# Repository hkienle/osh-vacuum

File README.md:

# Open Source Vacuum Cleaner

> **📝 Note:** This repository is currently being populated with information. Content and documentation are being added progressively.

---

## About

This repository contains the Open Source Vacuum Cleaner project, an open-source hardware and software solution for building custom vacuum cleaners. The project includes complete PCB designs, ESP32-S3 based firmware, and a web-based control interface.

The system is designed to control high RPM impellers for vacuum machines, featuring motor control, real-time monitoring (RPM, temperature, battery voltage), WiFi connectivity, and a modern web interface.

## Project Structure

```
osh-vacuum/
├── Hardware/                  # PCB designs and hardware documentation
│   ├── v1/                    # Benchtop prototype board (V1)
│   │   ├── README.md          # Hardware documentation and BOM
│   │   └── Production/        # Manufacturing files
│   └── v2/                    # V2 electronics (KiCad 10)
│       ├── README.md          # Overview, cabling, commit marking
│       ├── Main PCB/          # Control board, JLCPCB data in Production/
│       └── HMI PCB/           # Breakaway LED strips and buttons, JLCPCB data in Production/
├── Firmware/                  # ESP32-S3 firmware
│   ├── v1/                    # Firmware for hardware V1 (with React web interface in ui/)
│   └── v2/                    # Firmware for hardware V2 (not started yet)
└── README.md                  # This file
```

### Hardware

**V1 – benchtop prototype**
- ESP32-S3 microcontroller with WiFi and BLE
- Motor control with Infineon ProFet for high-side switching
- 5 RGB LEDs (WS2812B) and 3 customizable buttons
- Battery voltage monitoring (15-32V input)
- Temperature monitoring via thermistor
- Tachometer input for RPM measurement
- Break-off sections for flexible form factors

📖 **[Hardware V1 Documentation →](Hardware/v1/README.md)**

**V2 – main board and HMI boards** (first batch ordered November 2026, untested)
- Main PCB: XT60 battery input with fuse, TVS and current measurement (INA237), ESP32-S3 with USB-C, switched motor output (XT60) for an ESC, brush output, motor signal connector with selectable 3.3 V / 5 V level, 4 × Qwiic, NTC, expansion header
- HMI PCB: breakaway panel with two WS2812B LED strips and button boards, connected to the main board with JST PH cables

📖 **[Hardware V2 Documentation →](Hardware/v2/README.md)**

### Firmware

The firmware provides:
- Motor speed control (0-100% PWM)
- Real-time monitoring (RPM, temperature, battery voltage)
- WiFi access point with web server
- WebSocket communication for live updates
- React-based web interface

The firmware in [Firmware/v1](Firmware/v1/README.md) is written for hardware V1. Firmware for V2 will go into `Firmware/v2`.

📖 **[Firmware Documentation →](Firmware/v1/README.md)**

## Quick Start

1. **Hardware**: Review the PCB documentation for [V1](Hardware/v1/README.md) or [V2](Hardware/v2/README.md)
2. **Firmware**: Follow the [firmware build and upload instructions](Firmware/v1/Setup.md)
3. **Frontend**: Build and upload the web interface as described in the firmware README

## Status

**Current Phase**: Benchtop Prototype (V1), V2 boards ordered

The V2 boards (main board and HMI boards) are ordered but untested; firmware for V2 has not been started yet. All designs and firmware are provided as-is for development and testing purposes.

---

*More information at [HackMD - Team Intuity](https://hackmd.io/@team-intuity) and [HackMD - hkienle](https://hackmd.io/@hkienle)*

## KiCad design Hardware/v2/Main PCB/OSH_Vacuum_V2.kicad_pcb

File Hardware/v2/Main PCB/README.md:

# Main PCB (Hardware V2)

Control board of the vacuum cleaner: battery input, motor and brush switching, ESP32-S3, sensors and all connectors.
KiCad 10 project `OSH_Vacuum_V2.kicad_pro`, schematic as PDF in [OSH_Vacuum_V2.pdf](OSH_Vacuum_V2.pdf).

**Status:** first batch ordered at JLCPCB in November 2026, not yet tested.

## Board

- 68 × 90 mm, 4 layers, 1.6 mm, 2 oz outer / 1 oz inner copper
- All parts on the top side, all parts in stock at JLCPCB (LCSC number in every symbol)
- Four M3 mounting holes (plated, connected to GND)

## Blocks

| Schematic sheet | Content |
|---|---|
| `Versorgung.kicad_sch` (power) | XT60 battery input (J10), 25 A fuse, TVS, 1 mΩ shunt with INA237 (current and battery voltage), LMR36520 buck to 5 V, USB/5 V diode OR, LDL1117 3.3 V, AP2553 switched outputs |
| `MCU_USB.kicad_sch` | ESP32-S3-WROOM-1-N16R8, USB-C with ESD protection, reset and boot buttons |
| `Motor_Buerste.kicad_sch` (motor and brush) | High-side motor switch (LM74502 + MOSFET, soft start) to the motor XT60 (J20) for an ESC, brush output with P-MOSFET and freewheel diodes (terminal J22), status LEDs |
| `Motorsignale_I2C_NTC.kicad_sch` | Motor signal connector J61 (JST PH 5-pin): signal level V_MOT 3.3 V by default, 5 V selectable with JP60; level shifters and protected inputs. I2C bus with 4 × Qwiic/STEMMA QT, NTC input |
| `Bedienung_CAN_EXP.kicad_sch` (user interface, expansion) | WS2812B LED output J60, three buttons (on board and via JST PH J50–J52), expansion header 2 × 7 (J40) |

## Connectors to the HMI PCB

JST PH 2.0 mm, pinout 1:1 with the [HMI PCB](../HMI%20PCB/README.md), so use straight cables (pin 1 to pin 1):

| Connector | Pin 1 | Pin 2 | Pin 3 |
|---|---|---|---|
| LED (J60) | GND | Data | 5 V |
| Button (J50–J52) | Switch | GND | – |

A reversed cable swaps 5 V and GND on the LED strips.

## Files

| Path | Content |
|---|---|
| `OSH_Vacuum_V2.kicad_pro`, `*.kicad_sch`, `OSH_Vacuum_V2.kicad_pcb` | KiCad 10 project |
| `OSH_Bedien/Motor/Power.kicad_sym`, `OSH_Vacuum_V2.pretty/` | Project symbols and footprints (linked via `${KIPRJMOD}`) |
| `OSH_Vacuum_V2.3dshapes/` | 3D models that KiCad does not ship (JLCEDA/EasyEDA library or simplified approximations) |
| `Production/` | JLCPCB data: Gerber ZIP (plus unpacked `gerber/`), BOM, CPL |

## Ordering at JLCPCB

Upload `Production/OSH_Vacuum_V2_gerber.zip`, then BOM and CPL for assembly.

- 4 layers, 1.6 mm, 2 oz outer / 1 oz inner, vias plugged, min. via 0.3 / (0.4/0.45) mm
- PCBA top side, parts selected by customer, "Confirm Parts Placement": yes
- In the placement preview, check the orientation of all diodes, ICs and connectors before confirming.

The bottom silkscreen carries `COMMIT xxxxxxx`, see [Hardware V2](../README.md#commit-marking).

## Known issues

- **Boards marked `COMMIT 04D906B`:** on the bottom silkscreen, `+` and `−` are swapped at both XT60 connectors
  (BATTERY IN and MAIN (15A)). The upper pin (square pad) is **GND**, the lower pin is **+**. Only the print is wrong;
  copper and connectors are correct. Fixed in `31ACDF0`.

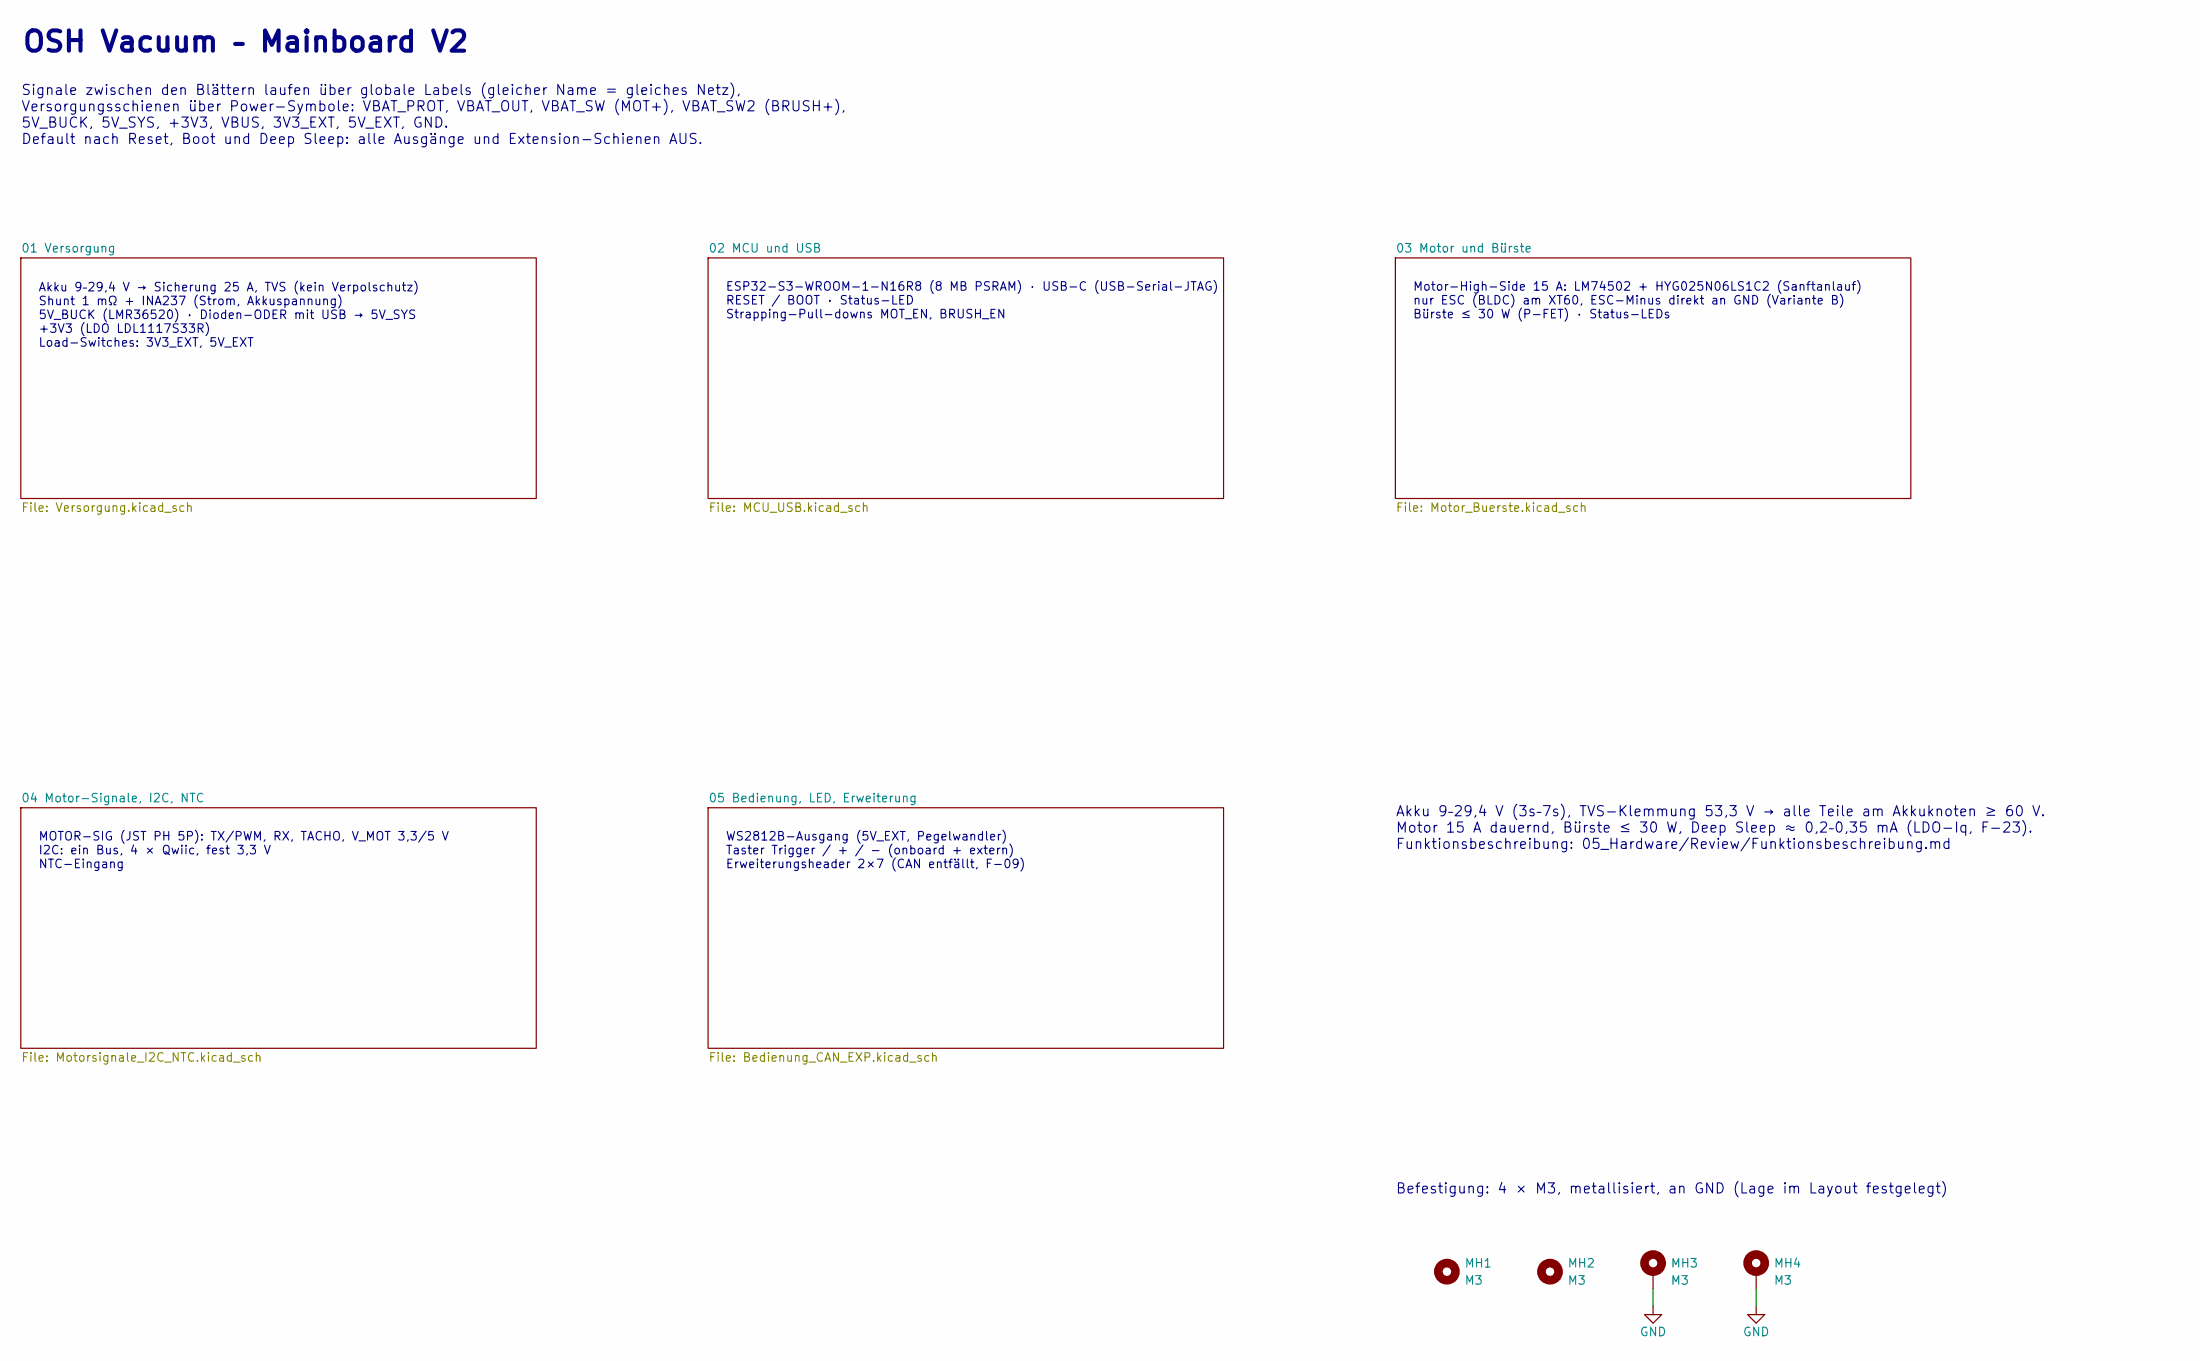
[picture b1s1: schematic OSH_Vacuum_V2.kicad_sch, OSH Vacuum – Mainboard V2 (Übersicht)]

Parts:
MH1, MH2: M3; MountingHole_3.2mm_M3_SilkRing
MH3, MH4: M3; MountingHole_3.2mm_M3_Pad_Via

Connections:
GND: MH3.1, MH4.1; also elsewhere on the board

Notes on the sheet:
ESP32-S3-WROOM-1-N16R8 (8 MB PSRAM) · USB-C (USB-Serial-JTAG) RESET / BOOT · Status-LED Strapping-Pull-downs MOT_EN, BRUSH_EN
OSH Vacuum – Mainboard V2
Motor-High-Side 15 A: LM74502 + HYG025N06LS1C2 (Sanftanlauf) nur ESC (BLDC) am XT60, ESC-Minus direkt an GND (Variante B) Bürste ≤ 30 W (P-FET) · Status-LEDs
Signale zwischen den Blättern laufen über globale Labels (gleicher Name = gleiches Netz), Versorgungsschienen über Power-Symbole: VBAT_PROT, VBAT_OUT, VBAT_SW (MOT+), VBAT_SW2 (BRUSH+), 5V_BUCK, 5V_SYS, +3V3, VBUS, 3V3_EXT, 5V_EXT, GND. Default nach Reset, Boot und Deep Sleep: alle Ausgänge und Ext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
MOTOR-SIG (JST PH 5P): TX/PWM, RX, TACHO, V_MOT 3,3/5 V I2C: ein Bus, 4 × Qwiic, fest 3,3 V NTC-Eingang
Akku 9–29,4 V (3s–7s), TVS-Klemmung 53,3 V → alle Teile am Akkuknoten ≥ 60 V. Motor 15 A dauernd, Bürste ≤ 30 W, Deep Sleep ≈ 0,2–0,35 mA (LDO-Iq, F-23). Funktionsbeschreibung: 05_Hardware/Review/Funktionsbeschreibung.md
WS2812B-Ausgang (5V_EXT, Pegelwandler) Taster Trigger / + / − (onboard + extern) Erweiterungsheader 2×7 (CAN entfällt, F-09)
Befestigung: 4 × M3, metallisiert, an GND (Lage im Layout festgelegt)
Akku 9–29,4 V → Sicherung 25 A, TVS (kein Verpolschutz) Shunt 1 mΩ + INA237 (Strom, Akkuspannung) 5V_BUCK (LMR36520) · Dioden-ODER mit USB → 5V_SYS +3V3 (LDO LDL1117S33R) Load-Switches: 3V3_EXT, 5V_EXT

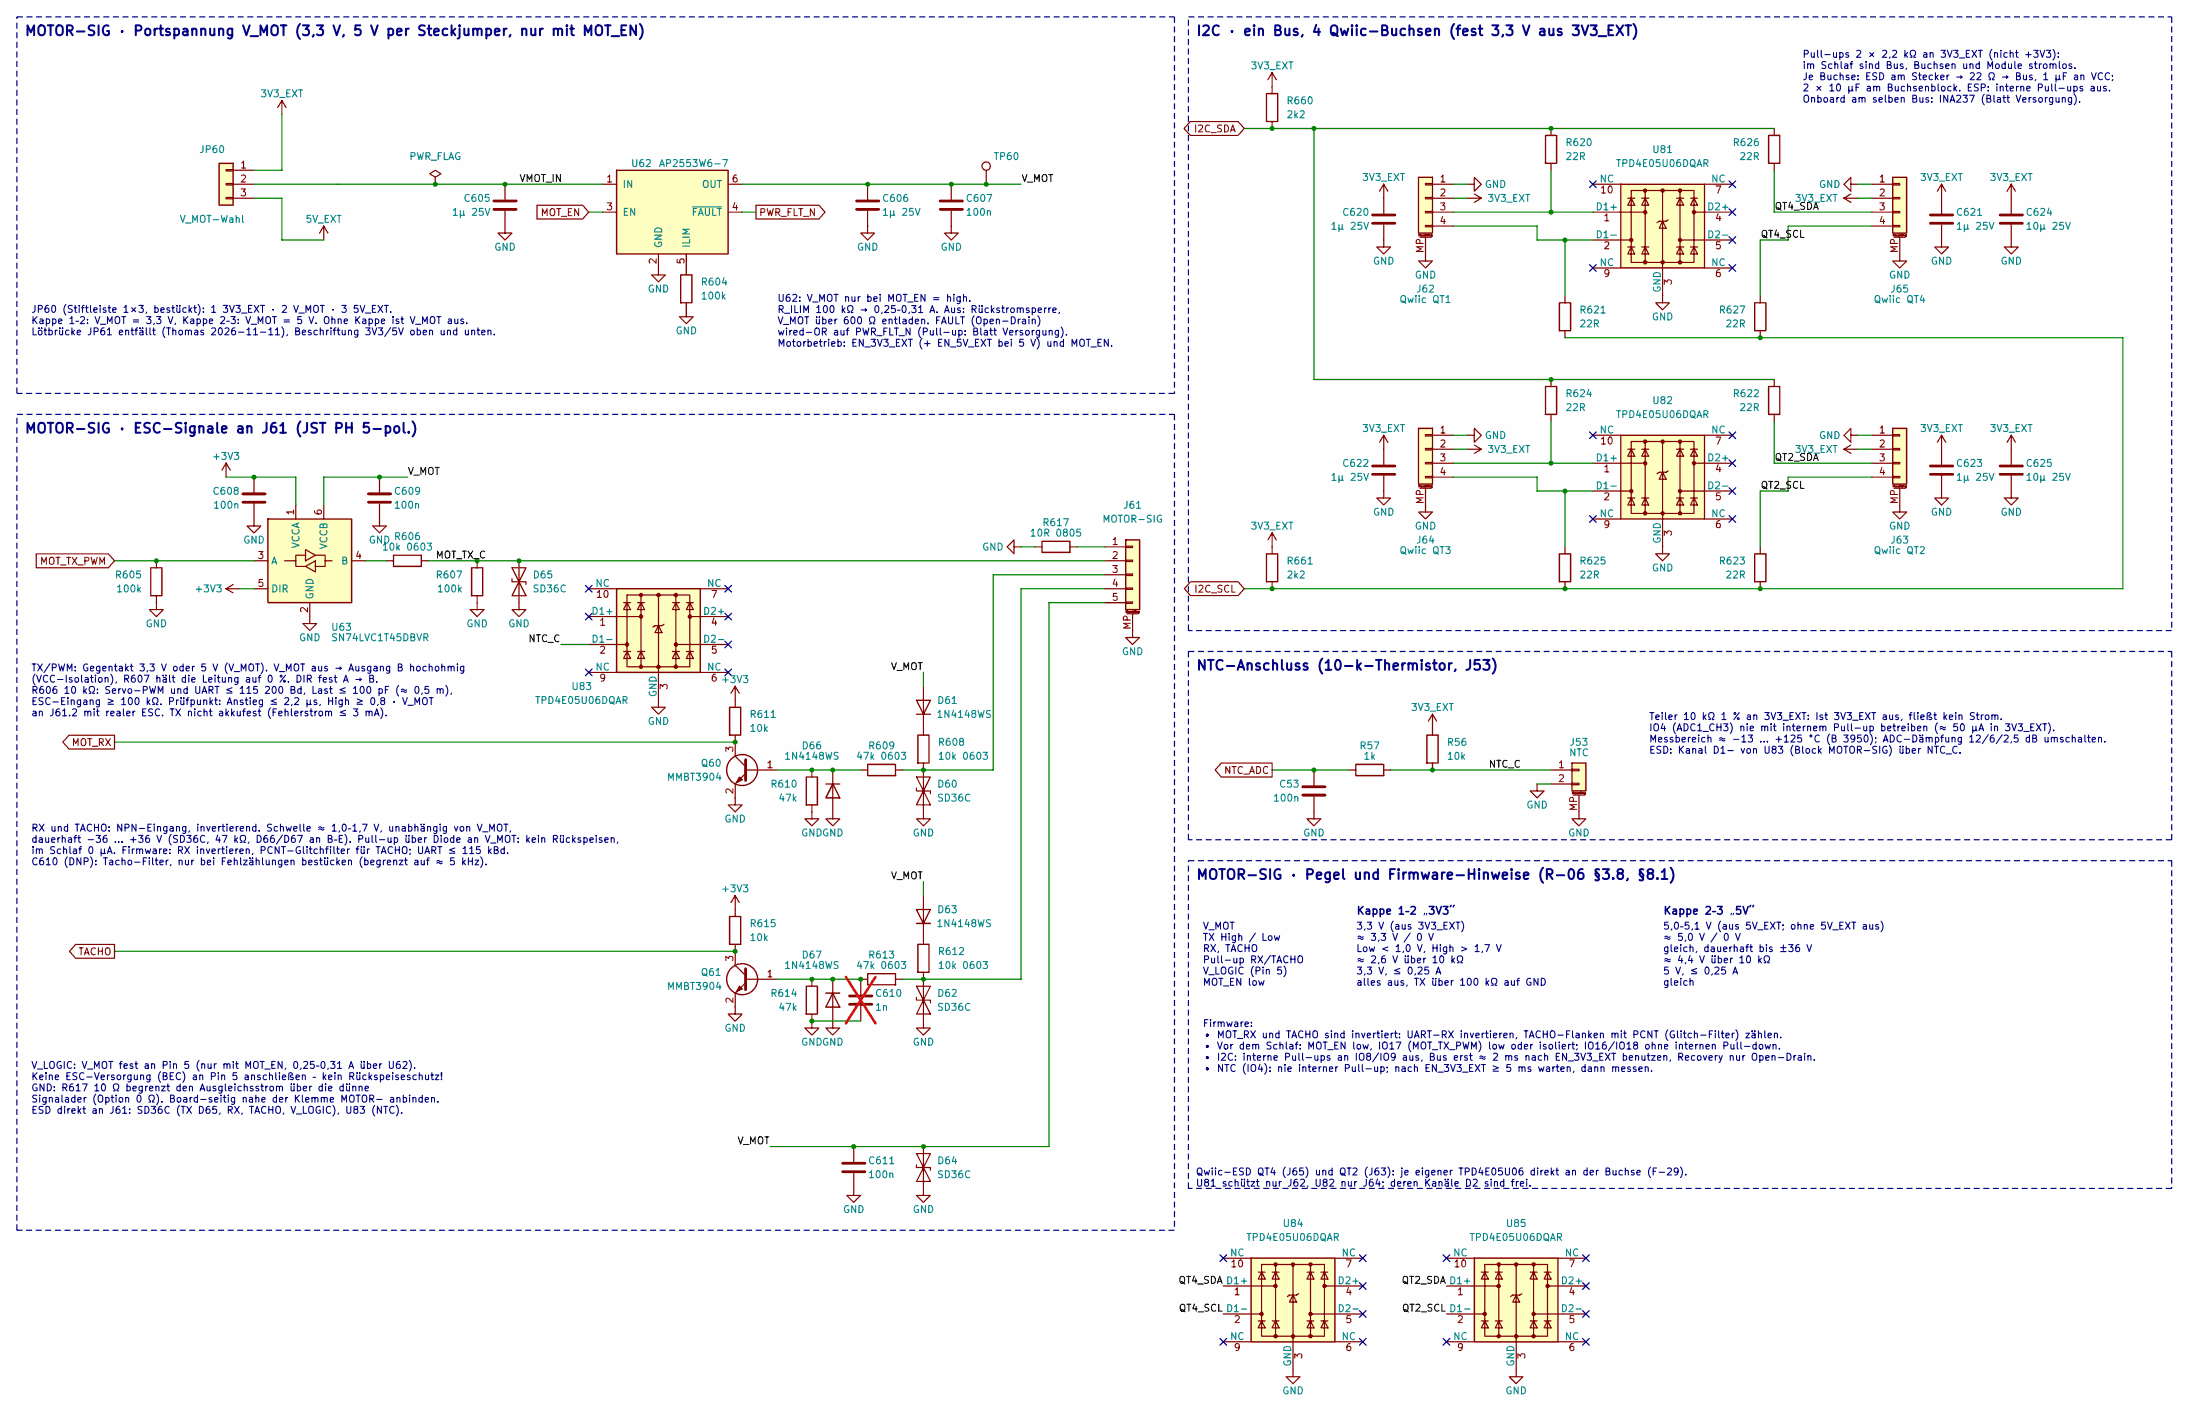
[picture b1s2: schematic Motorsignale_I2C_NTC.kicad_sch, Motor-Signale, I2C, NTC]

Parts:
C53, C607, C608, C609, C611: 100n; C_0402_1005Metric; MPN CL05B104KO5NNNC; LCSC C1525
C605, C606, C620, C621, C622, C623: 1µ 25V; C_0402_1005Metric; MPN CL05A105KA5NQNC; LCSC C52923
C610: 1n; C_0402_1005Metric; MPN 0402B102K500NT; LCSC C1523; not fitted
C624, C625: 10µ 25V; C_0805_2012Metric; MPN CL21A106KAYNNNE; LCSC C15850
D60, D62, D64, D65: SD36C; D_SOD-323; MPN SD36C; LCSC C502537
D61, D63, D66, D67: 1N4148WS; D_SOD-323; MPN 1N4148WS; LCSC C2128
J53: NTC; JST_PH_S2B-PH-SM4-TB_1x02-1MP_P2.00mm_Horizontal; MPN S2B-PH-SM4-TB(LF)(SN); LCSC C295747
J61: MOTOR-SIG; JST_PH_S5B-PH-SM4-TB_1x05-1MP_P2.00mm_Horizontal; MPN S5B-PH-SM4-TB(LF)(SN); LCSC C265104
J62: Qwiic QT1; Megastar_ZX-SH1.0-4PWT_1x04-1MP_P1.00mm_Horizontal; MPN ZX-SH1.0-4PWT; LCSC C7430446
J63: Qwiic QT2; Megastar_ZX-SH1.0-4PWT_1x04-1MP_P1.00mm_Horizontal; MPN ZX-SH1.0-4PWT; LCSC C7430446
J64: Qwiic QT3; Megastar_ZX-SH1.0-4PWT_1x04-1MP_P1.00mm_Horizontal; MPN ZX-SH1.0-4PWT; LCSC C7430446
J65: Qwiic QT4; Megastar_ZX-SH1.0-4PWT_1x04-1MP_P1.00mm_Horizontal; MPN ZX-SH1.0-4PWT; LCSC C7430446
JP60: V_MOT-Wahl; PinHeader_1x03_P2.54mm_Vertical; MPN B-2100S03P-A110; LCSC C124376
Q60, Q61: MMBT3904; SOT-23; MPN MMBT3904 (RANGE:100-300); LCSC C20526
R56, R611, R615: 10k; R_0402_1005Metric; MPN 0402WGF1002TCE; LCSC C25744
R57: 1k; R_0402_1005Metric; MPN 0402WGF1001TCE; LCSC C11702
R604, R605, R607: 100k; R_0402_1005Metric; MPN 0402WGF1003TCE; LCSC C25741
R606, R608, R612: 10k 0603; R_0603_1608Metric; MPN 0603WAF1002T5E; LCSC C25804
R609, R613: 47k 0603; R_0603_1608Metric; MPN 0603WAF4702T5E; LCSC C25819
R610, R614: 47k; R_0402_1005Metric; MPN 0402WGF4702TCE; LCSC C25792
R617: 10R 0805; R_0805_2012Metric; MPN 0805W8F100JT5E; LCSC C17415
R620, R621, R622, R623, R624, R625, R626, R627: 22R; R_0402_1005Metric; MPN 0402WGF220JTCE; LCSC C25092
R660, R661: 2k2; R_0402_1005Metric; MPN 0402WGF2201TCE; LCSC C25879
TP60: V_MOT; Testpad_D1.0mm
U62: AP2553W6-7; SOT-23-6; MPN AP2553W6-7; LCSC C212302
U63: SN74LVC1T45DBVR; SOT-23-6; MPN SN74LVC1T45DBVR; LCSC C7843
U81, U82, U83, U84, U85: TPD4E05U06DQAR; USON-10_2.5x1.0mm_P0.5mm; MPN TPD4E05U06DQAR; LCSC C138714

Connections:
3V3_EXT: C620.1, C621.1, C622.1, C623.1, C624.1, C625.1, J62.2, J63.2, J64.2, J65.2, JP60.1, R56.1, R660.1, R661.1; also elsewhere on the board
5V_EXT: JP60.3; also elsewhere on the board
+3V3: C608.1, R611.1, R615.1, U63.1 (VCCA), U63.5 (DIR); also elsewhere on the board
/04 Motor-Signale, I2C, NTC/MOT_TX_C: D65.1 (A1), J61.2, R606.2, R607.1
/04 Motor-Signale, I2C, NTC/NTC_C: J53.1, R56.2, R57.2, U83.2 (D1-)
/04 Motor-Signale, I2C, NTC/QT2_SCL: J63.4, R623.1, U85.2 (D1-)
/04 Motor-Signale, I2C, NTC/QT2_SDA: J63.3, R622.2, U85.1 (D1+)
/04 Motor-Signale, I2C, NTC/QT4_SCL: J65.4, R627.1, U84.2 (D1-)
/04 Motor-Signale, I2C, NTC/QT4_SDA: J65.3, R626.2, U84.1 (D1+)
/04 Motor-Signale, I2C, NTC/VMOT_IN: C605.1, JP60.2, U62.1 (IN)
/04 Motor-Signale, I2C, NTC/V_MOT: C606.1, C607.1, C609.1, C611.1, D61.2 (A), D63.2 (A), D64.1 (A1), J61.5, TP60.1, U62.6 (OUT), U63.6 (VCCB)
GND: C53.2, C605.2, C606.2, C607.2, C608.2, C609.2, C610.2, C611.2, C620.2, C621.2, C622.2, C623.2, C624.2, C625.2, D60.2 (A2), D62.2 (A2), D64.2 (A2), D65.2 (A2), D66.2 (A), D67.2 (A), J53.2, J53.MP (MountPin), J61.MP (MountPin), J62.1, J62.MP (MountPin), J63.1, J63.MP (MountPin), J64.1, J64.MP (MountPin), J65.1, J65.MP (MountPin), Q60.2 (E), Q61.2 (E), R604.2, R605.2, R607.2, R610.2, R614.2, R617.1, U62.2 (GND), U63.2 (GND), U81.3 (GND), U81.8 (GND), U82.3 (GND), U82.8 (GND), U83.3 (GND), U83.8 (GND), U84.3 (GND), U84.8 (GND), U85.3 (GND), U85.8 (GND); also elsewhere on the board
I2C_SCL: R621.2, R623.2, R625.2, R627.2, R661.2; also elsewhere on the board
I2C_SDA: R620.1, R622.1, R624.1, R626.1, R660.2; also elsewhere on the board
MOT_EN: U62.3 (EN); also elsewhere on the board
MOT_RX: Q60.3 (C), R611.2; also elsewhere on the board
MOT_TX_PWM: R605.1, U63.3 (A); also elsewhere on the board
NTC_ADC: C53.1, R57.1; also elsewhere on the board
unnamed: D60.1 (A1), J61.3, R608.2, R609.2
unnamed: D61.1 (K), R608.1
unnamed: D62.1 (A1), J61.4, R612.2, R613.2
unnamed: D63.1 (K), R612.1
unnamed: D66.1 (K), Q60.1 (B), R609.1, R610.1
unnamed: C610.1, D67.1 (K), Q61.1 (B), R613.1, R614.1
unnamed: J61.1, R617.2
unnamed: J62.3, R620.2, U81.1 (D1+)
unnamed: J62.4, R621.1, U81.2 (D1-)
unnamed: J64.3, R624.2, U82.1 (D1+)
unnamed: J64.4, R625.1, U82.2 (D1-)
unnamed: R604.1, U62.5 (ILIM)
unnamed: R606.1, U63.4 (B)
PWR_FLT_N: U62.4 (~FAULT); also elsewhere on the board
TACHO: Q61.3 (C), R615.2; also elsewhere on the board

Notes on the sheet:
MOTOR-SIG · Portspannung V_MOT (3,3 V, 5 V per Steckjumper, nur mit MOT_EN)
Qwiic-ESD QT4 (J65) und QT2 (J63): je eigener TPD4E05U06 direkt an der Buchse (F-29). U81 schützt nur J62, U82 nur J64; deren Kanäle D2 sind frei.
Pull-ups 2 × 2,2 kΩ an 3V3_EXT (nicht +3V3): im Schlaf sind Bus, Buchsen und Module stromlos. Je Buchse: ESD am Stecker → 22 Ω → Bus, 1 µF an VCC; 2 × 10 µF am Buchsenblock. ESP: interne Pull-ups aus. Onboard am selben Bus: INA237 (Blatt Versorgung).
I2C · ein Bus, 4 Qwiic-Buchsen (fest 3,3 V aus 3V3_EXT)
RX und TACHO: NPN-Eingang, invertierend. Schwelle ≈ 1,0–1,7 V, unabhängig von V_MOT, dauerhaft −36 … +36 V (SD36C, 47 kΩ, D66/D67 an B–E). Pull-up über Diode an V_MOT: kein Rückspeisen, im Schlaf 0 µA. Firmware: RX invertieren, PCNT-Glitchfilter für TACHO; UART ≤ 115 kBd. C610 (DNP): Tacho-Filter, 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
MOTOR-SIG · ESC-Signale an J61 (JST PH 5-pol.)
JP60 (Stiftleiste 1×3, bestückt): 1 3V3_EXT · 2 V_MOT · 3 5V_EXT. Kappe 1–2: V_MOT = 3,3 V, Kappe 2–3: V_MOT = 5 V. Ohne Kappe ist V_MOT aus. Lötbrücke JP61 entfällt (Thomas 2026-11-11), Beschriftung 3V3/5V oben und unten.
U62: V_MOT nur bei MOT_EN = high. R_ILIM 100 kΩ → 0,25–0,31 A. Aus: Rückstromsperre, V_MOT über 600 Ω entladen. FAULT (Open-Drain) wired-OR auf PWR_FLT_N (Pull-up: Blatt Versorgung). Motorbetrieb: EN_3V3_EXT (+ EN_5V_EXT bei 5 V) und MOT_EN.
Kappe 1–2 „3V3“
5,0–5,1 V (aus 5V_EXT; ohne 5V_EXT aus) ≈ 5,0 V / 0 V gleich, dauerhaft bis ±36 V ≈ 4,4 V über 10 kΩ 5 V, ≤ 0,25 A gleich
V_MOT TX High / Low RX, TACHO Pull-up RX/TACHO V_LOGIC (Pin 5) MOT_EN low
NTC-Anschluss (10-k-Thermistor, J53)
Kappe 2–3 „5V“
TX/PWM: Gegentakt 3,3 V oder 5 V (V_MOT). V_MOT aus → Ausgang B hochohmig (VCC-Isolation), R607 hält die Leitung auf 0 %. DIR fest A → B. R606 10 kΩ: Servo-PWM und UART ≤ 115 200 Bd, Last ≤ 100 pF (≈ 0,5 m), ESC-Eingang ≥ 100 kΩ. Prüfpunkt: Anstieg ≤ 2,2 µs, High ≥ 0,8 · V_MOT an J61.2 mit realer E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
Teiler 10 kΩ 1 % an 3V3_EXT: Ist 3V3_EXT aus, fließt kein Strom. IO4 (ADC1_CH3) nie mit internem Pull-up betreiben (≈ 50 µA in 3V3_EXT). Messbereich ≈ −13 … +125 °C (B 3950); ADC-Dämpfung 12/6/2,5 dB umschalten. ESD: Kanal D1− von U83 (Block MOTOR-SIG) über NTC_C.
Firmware: • MOT_RX und TACHO sind invertiert: UART-RX invertieren, TACHO-Flanken mit PCNT (Glitch-Filter) zählen. • Vor dem Schlaf: MOT_EN low, IO17 (MOT_TX_PWM) low oder isoliert; IO16/IO18 ohne internen Pull-down. • I2C: interne Pull-ups an IO8/IO9 aus, Bus erst ≈ 2 ms nach EN_3V3_EXT benutzen, R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
3,3 V (aus 3V3_EXT) ≈ 3,3 V / 0 V Low < 1,0 V, High > 1,7 V ≈ 2,6 V über 10 kΩ 3,3 V, ≤ 0,25 A alles aus, TX über 100 kΩ auf GND
MOTOR-SIG · Pegel und Firmware-Hinweise (R-06 §3.8, §8.1)
V_LOGIC: V_MOT fest an Pin 5 (nur mit MOT_EN, 0,25–0,31 A über U62). Keine ESC-Versorgung (BEC) an Pin 5 anschließen – kein Rückspeiseschutz! GND: R617 10 Ω begrenzt den Ausgleichsstrom über die dünne Signalader (Option 0 Ω). Board-seitig nahe der Klemme MOTOR− anbinden. ESD direkt an J61: SD36C (T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

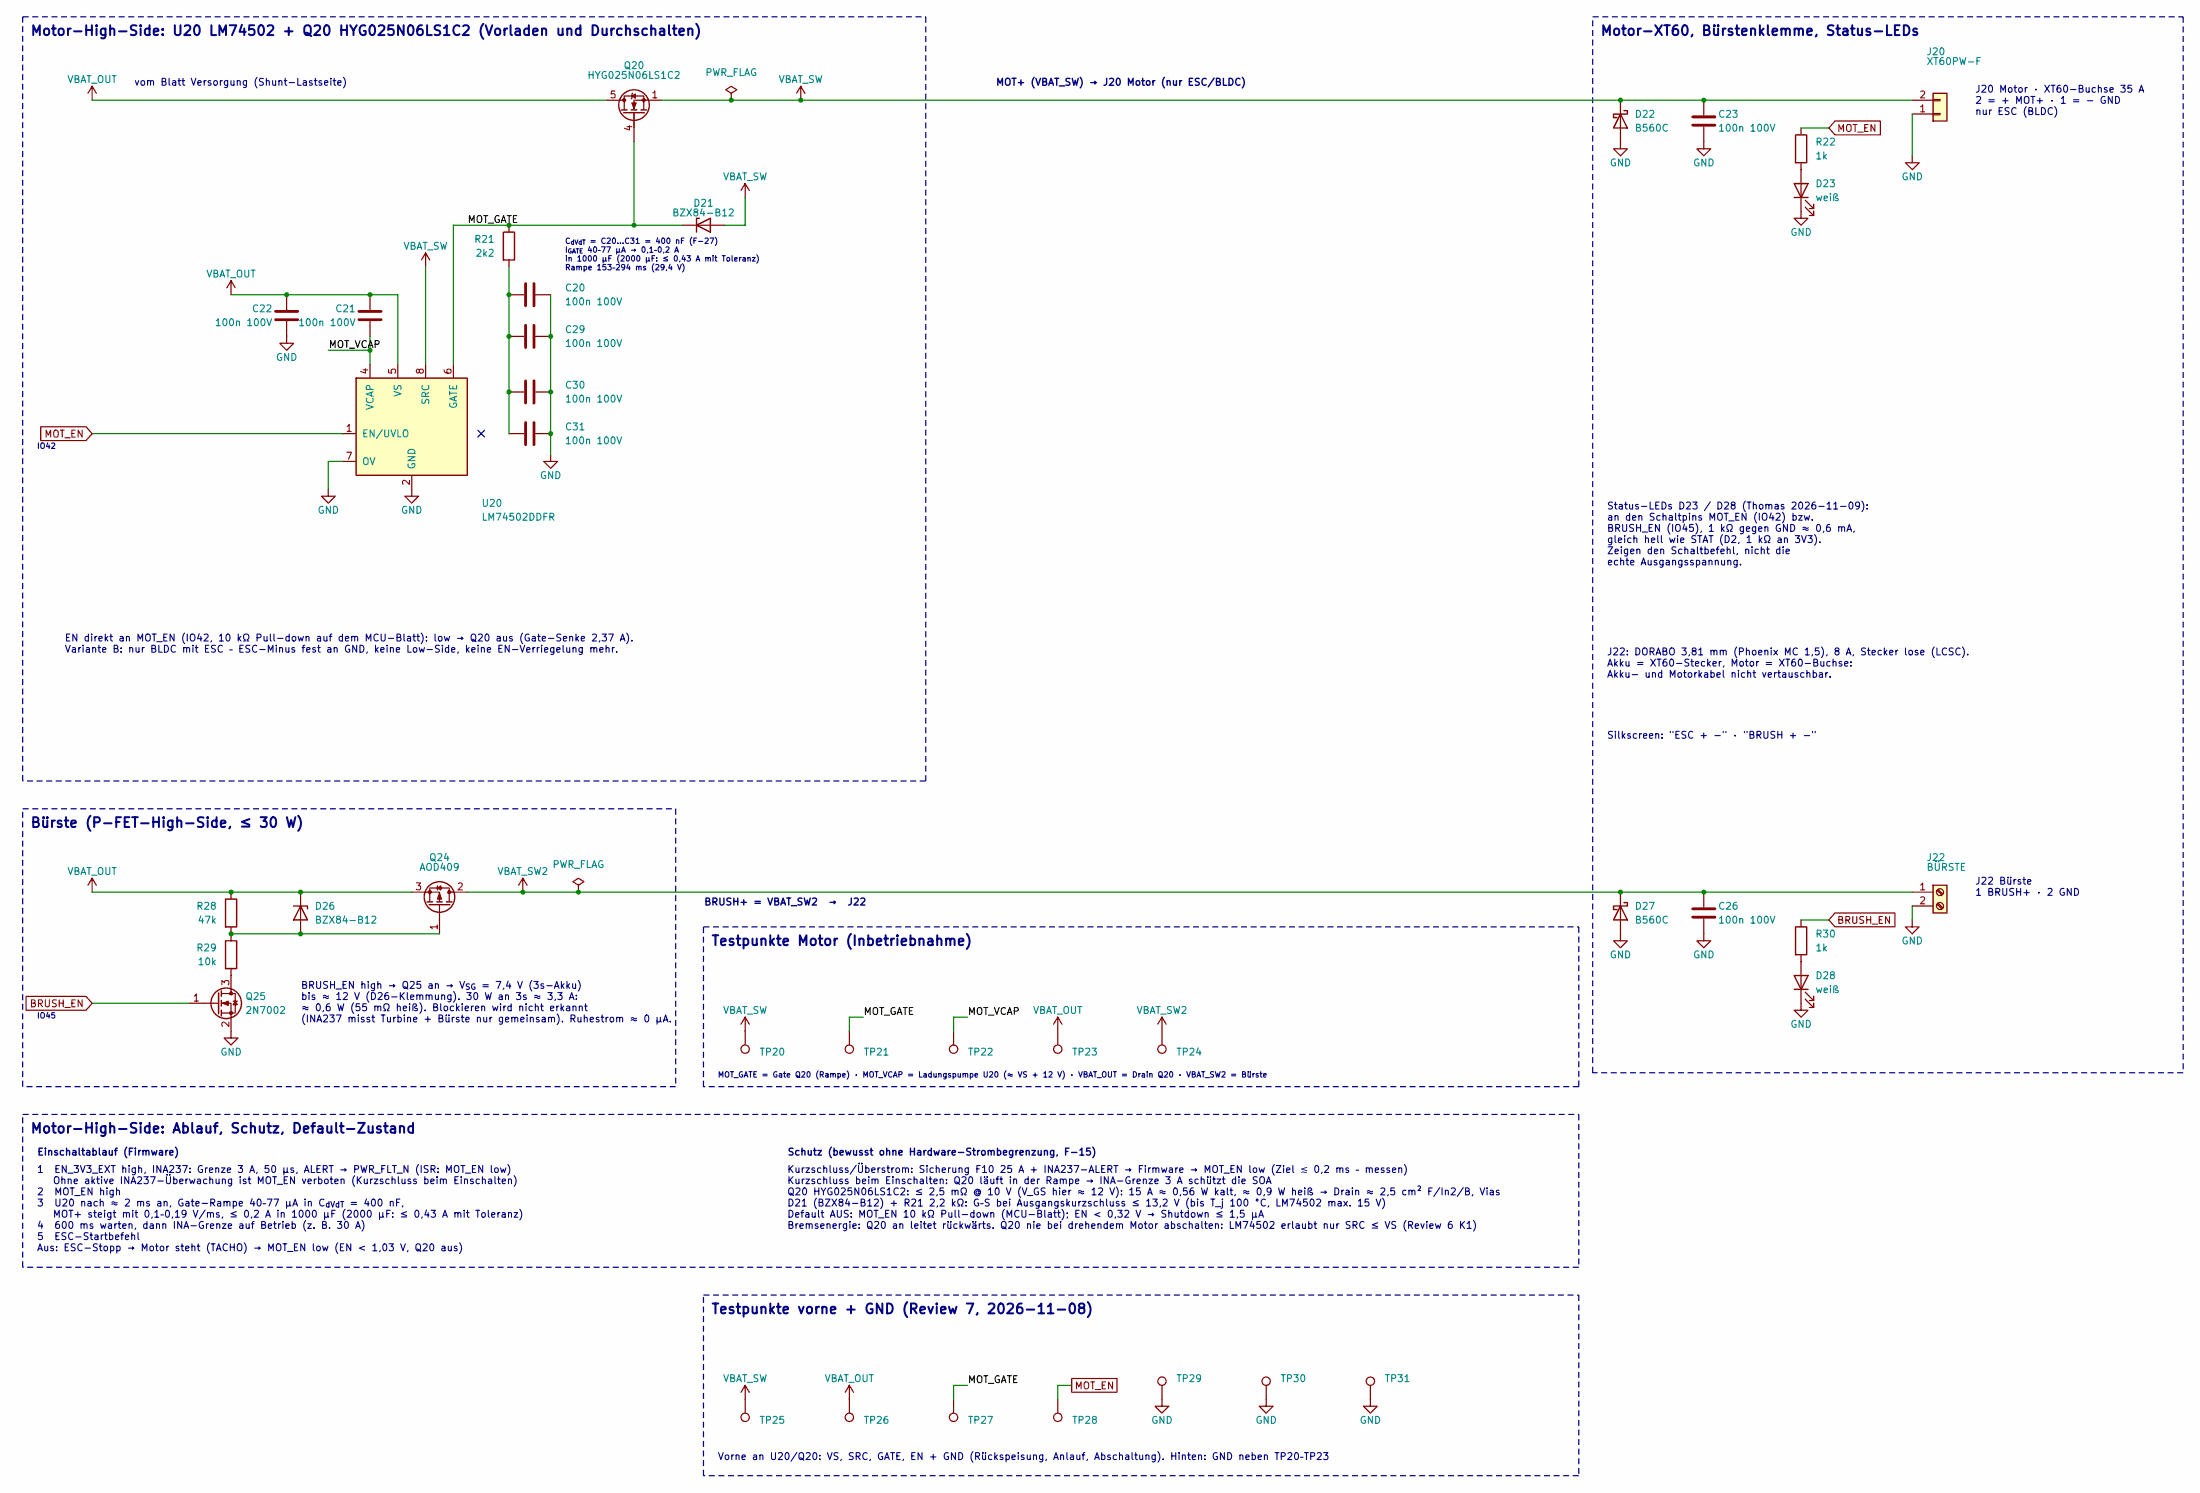
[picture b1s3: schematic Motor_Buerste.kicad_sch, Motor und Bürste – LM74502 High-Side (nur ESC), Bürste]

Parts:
C20, C21, C22, C23, C26, C29, C30, C31: 100n 100V; C_0805_2012Metric; MPN CL21B104KCFNNNE; LCSC C28233
D21, D26: BZX84-B12; SOT-23; MPN BZX84-B12,215; LCSC C282540
D22, D27: B560C; D_SMC; MPN B560C-13-F; LCSC C85100
D23, D28: weiß; LED_0603_1608Metric; MPN KT-0603W; LCSC C2290
J20: XT60PW-F; AMASS_XT60PW-F_1x02_P7.20mm_Horizontal; MPN XT60PW-F; LCSC C428722
J22: BÜRSTE; DORABO_DB2ERC-3.81-2P_P3.81mm_Horizontal; MPN DB2ERC-3.81-2P-GN; LCSC C395684
Q20: HYG025N06LS1C2; TDSON-8-1; MPN HYG025N06LS1C2; LCSC C2827231
Q24: AOD409; TO-252-2; MPN AOD409; LCSC C36220
Q25: 2N7002; SOT-23; MPN 2N7002; LCSC C8545
R21: 2k2; R_0402_1005Metric; MPN 0402WGF2201TCE; LCSC C25879
R22, R30: 1k; R_0603_1608Metric; MPN 0603WAF1001T5E; LCSC C21190
R28: 47k; R_0402_1005Metric; MPN 0402WGF4702TCE; LCSC C25792
R29: 10k; R_0603_1608Metric; MPN 0603WAF1002T5E; LCSC C25804
TP20, TP25: VBAT_SW; Testpad_D1.0mm
TP21, TP27: MOT_GATE; Testpad_D1.0mm
TP22: MOT_VCAP; Testpad_D1.0mm
TP23, TP26: VBAT_OUT; Testpad_D1.0mm
TP24: VBAT_SW2; Testpad_D1.0mm
TP28: MOT_EN; Testpad_D1.0mm
TP29: GND; Testpad_D1.0mm
TP30, TP31: GND; Testpad_D1.5mm
U20: LM74502DDFR; TSOT-23-8; MPN LM74502DDFR; LCSC C3236215

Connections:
/03 Motor und Bürste/MOT_GATE: D21.3 (K), Q20.4 (G), R21.1, TP21.1, TP27.1, U20.6 (GATE)
/03 Motor und Bürste/MOT_VCAP: C21.2, TP22.1, U20.4 (VCAP)
BRUSH_EN: Q25.1 (G), R30.1; also elsewhere on the board
GND: C20.2, C22.2, C23.2, C26.2, C29.2, C30.2, C31.2, D22.2 (A), D23.1 (K), D27.2 (A), D28.1 (K), J20.1, J22.2, Q25.2 (S), TP29.1, TP30.1, TP31.1, U20.2 (GND), U20.7 (OV); also elsewhere on the board
MOT_EN: R22.1, TP28.1, U20.1 (EN/UVLO); also elsewhere on the board
unnamed: C20.1, C29.1, C30.1, C31.1, R21.2
unnamed: D23.2 (A), R22.2
unnamed: D26.1 (A), Q24.1 (G), R28.2, R29.1
unnamed: D28.2 (A), R30.2
unnamed: Q25.3 (D), R29.2
VBAT_OUT: C21.1, C22.1, D26.3 (K), Q20.5 (D), Q24.3 (S), R28.1, TP23.1, TP26.1, U20.5 (VS); also elsewhere on the board
VBAT_SW: C23.1, D21.1 (A), D22.1 (K), J20.2, Q20.1 (S), Q20.2 (S), Q20.3 (S), TP20.1, TP25.1, U20.8 (SRC)
VBAT_SW2: C26.1, D27.1 (K), J22.1, Q24.2 (D), TP24.1

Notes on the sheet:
BRUSH+ = VBAT_SW2 → J22
Motor-High-Side: Ablauf, Schutz, Default-Zustand
EN direkt an MOT_EN (IO42, 10 kΩ Pull-down auf dem MCU-Blatt): low → Q20 aus (Gate-Senke 2,37 A). Variante B: nur BLDC mit ESC – ESC-Minus fest an GND, keine Low-Side, keine EN-Verriegelung mehr.
Kurzschluss/Überstrom: Sicherung F10 25 A + INA237-ALERT → Firmware → MOT_EN low (Ziel ≲ 0,2 ms – messen) Kurzschluss beim Einschalten: Q20 läuft in der Rampe → INA-Grenze 3 A schützt die SOA Q20 HYG025N06LS1C2: ≤ 2,5 mΩ @ 10 V (V_GS hier ≈ 12 V): 15 A ≈ 0,56 W kalt, ≈ 0,9 W heiß → Drain ≈ 2,5 cm² 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
IO42
Status-LEDs D23 / D28 (Thomas 2026-11-09): an den Schaltpins MOT_EN (IO42) bzw. BRUSH_EN (IO45), 1 kΩ gegen GND ≈ 0,6 mA, gleich hell wie STAT (D2, 1 kΩ an 3V3). Zeigen den Schaltbefehl, nicht die echte Ausgangsspannung.
Motor-High-Side: U20 LM74502 + Q20 HYG025N06LS1C2 (Vorladen und Durchschalten)
Silkscreen: "ESC + −" · "BRUSH + −"
C_{dVdT} = C20…C31 = 400 nF (F-27) I_{GATE} 40–77 µA → 0,1–0,2 A in 1000 µF (2000 µF: ≤ 0,43 A mit Toleranz) Rampe 153–294 ms (29,4 V)
1 EN_3V3_EXT high, INA237: Grenze 3 A, 50 µs, ALERT → PWR_FLT_N (ISR: MOT_EN low) Ohne aktive INA237-Überwachung ist MOT_EN verboten (Kurzschluss beim Einschalten) 2 MOT_EN high 3 U20 nach ≈ 2 ms an, Gate-Rampe 40–77 µA in C_{dVdT} = 400 nF, MOT+ steigt mit 0,1–0,19 V/ms, ≤ 0,2 A in 1000 µF (2000 µ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
MOT+ (VBAT_SW) → J20 Motor (nur ESC/BLDC)
Motor-XT60, Bürstenklemme, Status-LEDs
J22 Bürste 1 BRUSH+ · 2 GND
J20 Motor · XT60-Buchse 35 A 2 = + MOT+ · 1 = − GND nur ESC (BLDC)
Bürste (P-FET-High-Side, ≤ 30 W)
IO45
Einschaltablauf (Firmware)
Testpunkte vorne + GND (Review 7, 2026-11-08)
BRUSH_EN high → Q25 an → V_{SG} = 7,4 V (3s-Akku) bis ≈ 12 V (D26-Klemmung). 30 W an 3s ≈ 3,3 A: ≈ 0,6 W (55 mΩ heiß). Blockieren wird nicht erkannt (INA237 misst Turbine + Bürste nur gemeinsam). Ruhestrom ≈ 0 µA.
MOT_GATE = Gate Q20 (Rampe) · MOT_VCAP = Ladungspumpe U20 (≈ VS + 12 V) · VBAT_OUT = Drain Q20 · VBAT_SW2 = Bürste
Vorne an U20/Q20: VS, SRC, GATE, EN + GND (Rückspeisung, Anlauf, Abschaltung). Hinten: GND neben TP20–TP23
vom Blatt Versorgung (Shunt-Lastseite)
J22: DORABO 3,81 mm (Phoenix MC 1,5), 8 A, Stecker lose (LCSC). Akku = XT60-Stecker, Motor = XT60-Buchse: Akku- und Motorkabel nicht vertauschbar.
Schutz (bewusst ohne Hardware-Strombegrenzung, F-15)
Testpunkte Motor (Inbetriebnahme)

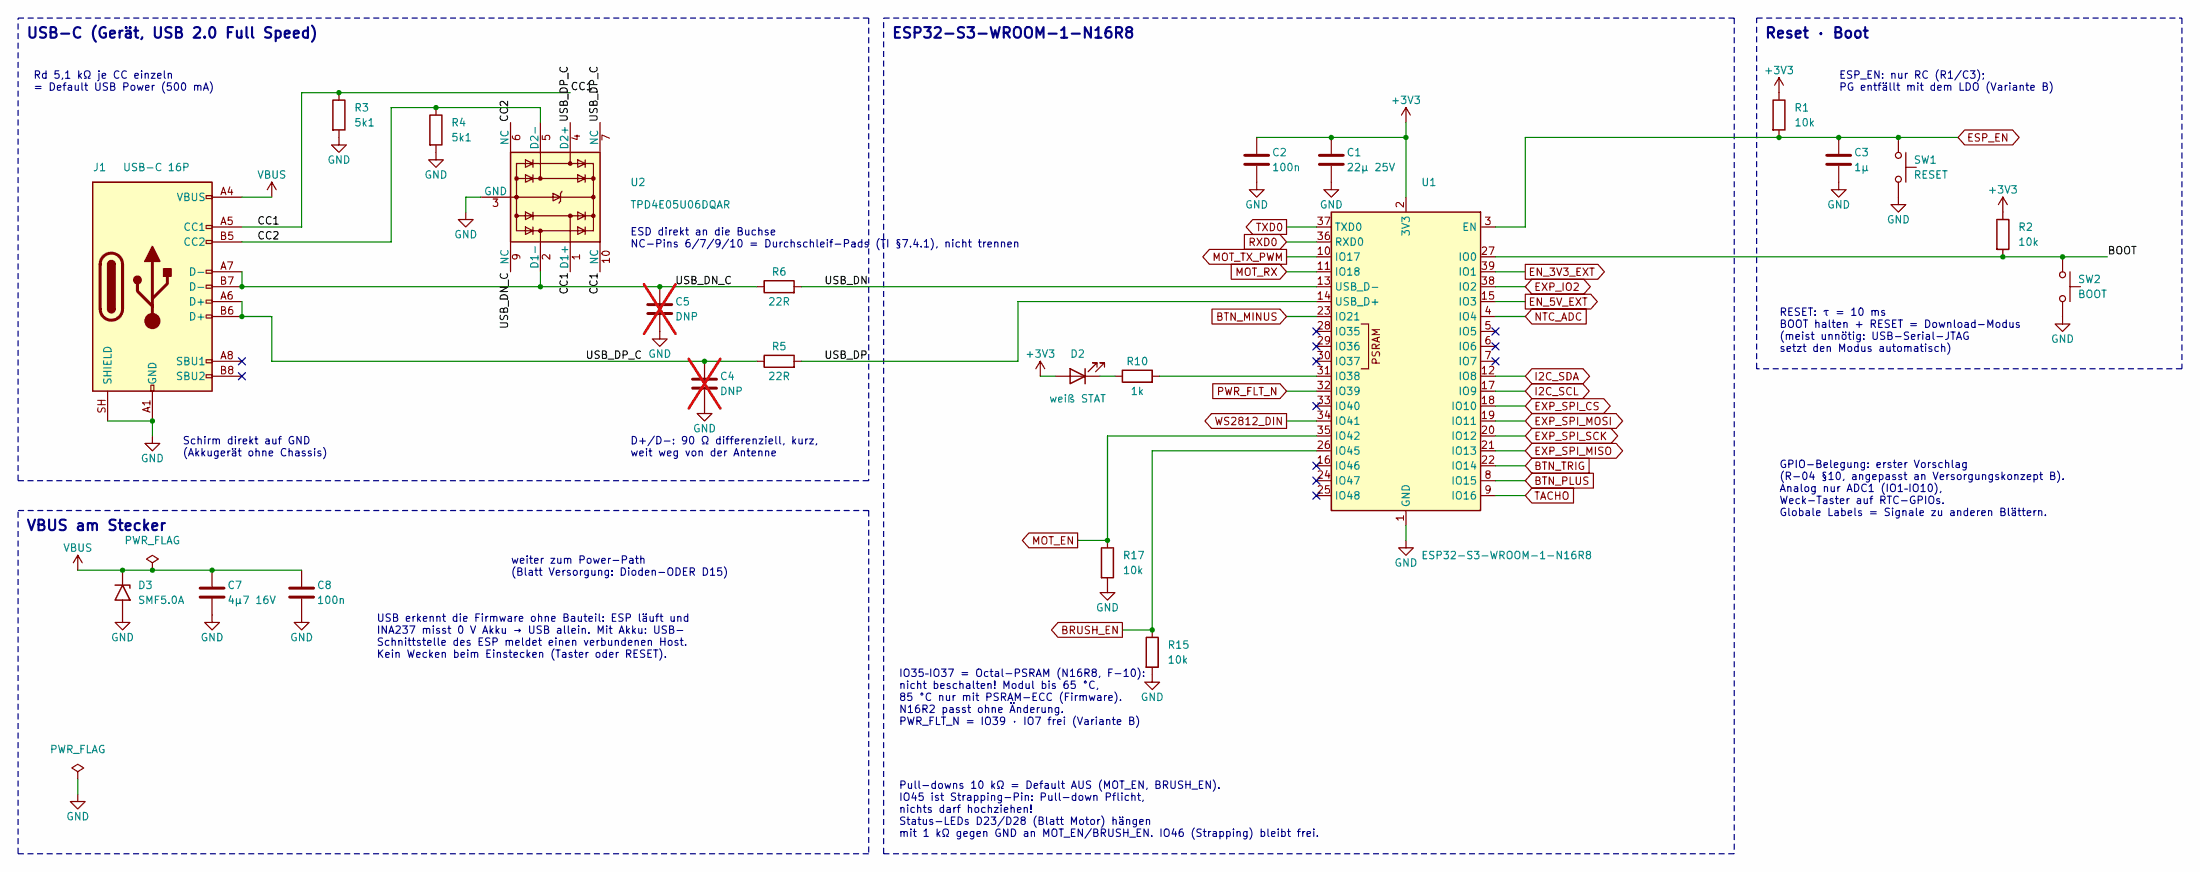
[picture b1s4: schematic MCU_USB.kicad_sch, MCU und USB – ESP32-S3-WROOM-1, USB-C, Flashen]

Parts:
C1: 22µ 25V; C_0805_2012Metric; MPN CL21A226MAQNNNE; LCSC C45783
C2, C8: 100n; C_0402_1005Metric; MPN CL05B104KO5NNNC; LCSC C1525
C3: 1µ; C_0402_1005Metric; MPN CL05A105KA5NQNC; LCSC C52923
C4, C5: DNP; C_0402_1005Metric; not fitted
C7: 4µ7 16V; C_0603_1608Metric; MPN CL10A475KO8NNNC; LCSC C19666
D2: weiß STAT; LED_0603_1608Metric; MPN KT-0603W; LCSC C2290
D3: SMF5.0A; D_SOD-123F; MPN SMF5.0A; LCSC C193402
J1: USB-C 16P; USB_C_Receptacle_HRO_TYPE-C-31-M-12; MPN TYPE-C-31-M-12; LCSC C165948
R1, R2, R15, R17: 10k; R_0402_1005Metric; MPN 0402WGF1002TCE; LCSC C25744
R3, R4: 5k1; R_0402_1005Metric; MPN 0402WGF5101TCE; LCSC C25905
R5, R6: 22R; R_0402_1005Metric; MPN 0402WGF220JTCE; LCSC C25092
R10: 1k; R_0402_1005Metric; MPN 0402WGF1001TCE; LCSC C11702
SW1: RESET; SW_SPST_TS-1088-xR020; MPN TS-1088-AR02016; LCSC C720477
SW2: BOOT; SW_SPST_TS-1088-xR020; MPN TS-1088-AR02016; LCSC C720477
U1: ESP32-S3-WROOM-1-N16R8; ESP32-S3-WROOM-1; MPN ESP32-S3-WROOM-1-N16R8; LCSC C2913202
U2: TPD4E05U06DQAR; USON-10_2.5x1.0mm_P0.5mm; MPN TPD4E05U06DQAR; LCSC C138714

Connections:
+3V3: C1.1, C2.1, D2.2 (A), R1.1, R2.1, U1.2 (3V3); also elsewhere on the board
/02 MCU und USB/BOOT: R2.2, SW2.1, U1.27 (IO0)
/02 MCU und USB/CC1: J1.A5 (CC1), R3.1, U2.1 (D1+), U2.10 (NC)
/02 MCU und USB/CC2: J1.B5 (CC2), R4.1, U2.5 (D2-), U2.6 (NC)
/02 MCU und USB/USB_DN: R6.2, U1.13 (USB_D-)
/02 MCU und USB/USB_DN_C: C5.1, J1.A7 (D-), J1.B7 (D-), R6.1, U2.2 (D1-), U2.9 (NC)
/02 MCU und USB/USB_DP: R5.2, U1.14 (USB_D+)
/02 MCU und USB/USB_DP_C: C4.1, J1.A6 (D+), J1.B6 (D+), R5.1, U2.4 (D2+), U2.7 (NC)
BRUSH_EN: R15.1, U1.26 (IO45); also elsewhere on the board
BTN_MINUS: U1.23 (IO21); also elsewhere on the board
BTN_PLUS: U1.8 (IO15); also elsewhere on the board
BTN_TRIG: U1.22 (IO14); also elsewhere on the board
EN_3V3_EXT: U1.39 (IO1); also elsewhere on the board
EN_5V_EXT: U1.15 (IO3); also elsewhere on the board
ESP_EN: C3.1, R1.2, SW1.1, U1.3 (EN)
EXP_IO2: U1.38 (IO2); also elsewhere on the board
EXP_SPI_CS: U1.18 (IO10); also elsewhere on the board
EXP_SPI_MISO: U1.21 (IO13); also elsewhere on the board
EXP_SPI_MOSI: U1.19 (IO11); also elsewhere on the board
EXP_SPI_SCK: U1.20 (IO12); also elsewhere on the board
GND: C1.2, C2.2, C3.2, C4.2, C5.2, C7.2, C8.2, D3.2 (A2), J1.A1 (GND), J1.A12 (GND), J1.B1 (GND), J1.B12 (GND), J1.SH (SHIELD), R3.2, R4.2, R15.2, R17.2, SW1.2, SW2.2, U1.1 (GND), U1.40 (GND), U1.41 (GND), U2.3 (GND), U2.8 (GND); also elsewhere on the board
I2C_SCL: U1.17 (IO9); also elsewhere on the board
I2C_SDA: U1.12 (IO8); also elsewhere on the board
MOT_EN: R17.1, U1.35 (IO42); also elsewhere on the board
MOT_RX: U1.11 (IO18); also elsewhere on the board
MOT_TX_PWM: U1.10 (IO17); also elsewhere on the board
NTC_ADC: U1.4 (IO4); also elsewhere on the board
unnamed: D2.1 (K), R10.1
unnamed: R10.2, U1.31 (IO38)
PWR_FLT_N: U1.32 (IO39); also elsewhere on the board
RXD0: U1.36 (RXD0); also elsewhere on the board
TACHO: U1.9 (IO16); also elsewhere on the board
TXD0: U1.37 (TXD0); also elsewhere on the board
VBUS: C7.1, C8.1, D3.1 (A1), J1.A4 (VBUS), J1.A9 (VBUS), J1.B4 (VBUS), J1.B9 (VBUS); also elsewhere on the board
WS2812_DIN: U1.34 (IO41); also elsewhere on the board

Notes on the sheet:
D+/D−: 90 Ω differenziell, kurz, weit weg von der Antenne
USB-C (Gerät, USB 2.0 Full Speed)
VBUS am Stecker
ESD direkt an die Buchse NC-Pins 6/7/9/10 = Durchschleif-Pads (TI §7.4.1), nicht trennen
RESET: τ = 10 ms BOOT halten + RESET = Download-Modus (meist unnötig: USB-Serial-JTAG setzt den Modus automatisch)
ESP_EN: nur RC (R1/C3); PG entfällt mit dem LDO (Variante B)
IO35–IO37 = Octal-PSRAM (N16R8, F-10): nicht beschalten! Modul bis 65 °C, 85 °C nur mit PSRAM-ECC (Firmware). N16R2 passt ohne Änderung. PWR_FLT_N = IO39 · IO7 frei (Variante B)
GPIO-Belegung: erster Vorschlag (R-04 §10, angepasst an Versorgungskonzept B). Analog nur ADC1 (IO1–IO10), Weck-Taster auf RTC-GPIOs. Globale Labels = Signale zu anderen Blättern.
Pull-downs 10 kΩ = Default AUS (MOT_EN, BRUSH_EN). IO45 ist Strapping-Pin: Pull-down Pflicht, nichts darf hochziehen! Status-LEDs D23/D28 (Blatt Motor) hängen mit 1 kΩ gegen GND an MOT_EN/BRUSH_EN. IO46 (Strapping) bleibt frei.
ESP32-S3-WROOM-1-N16R8
Schirm direkt auf GND (Akkugerät ohne Chassis)
weiter zum Power-Path (Blatt Versorgung: Dioden-ODER D15)
Reset · Boot
USB erkennt die Firmware ohne Bauteil: ESP läuft und INA237 misst 0 V Akku → USB allein. Mit Akku: USB- Schnittstelle des ESP meldet einen verbundenen Host. Kein Wecken beim Einstecken (Taster oder RESET).
Rd 5,1 kΩ je CC einzeln = Default USB Power (500 mA)
